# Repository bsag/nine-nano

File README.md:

# Nine keyboard

The Nine is a tiny 18-key split, wireless, ergonomic split keyboard, heavily inspired by Ben Vallack's [Piano 2](https://www.pcbway.com/project/shareproject/The_Piano_by_Ben_Vallack_Ultra_minimal_18_key_keyboard_5b2c99e1.html). I tried out his design and loved it, but wanted to [tweak the physical layout](https://www.rousette.org.uk/archives/introducing-the-nine-keyboard/) a bit to fit my hands and my use case better. It uses Nice!Nano V2 BLE-equipped controllers, and (optionally) Nice!View displays to show information like the connected BLE profile, battery level and layer name. You can read more about this keyboard and the design decisions I made here: [Introducing the Nine keyboard](https://www.rousette.org.uk/archives/introducing-the-nine-keyboard/) and [Nine keyboard Part 2 - the case](https://www.rousette.org.uk/archives/nine-keyboard-part-2-the-case/).

The PCB was generously sponsored by [PCBWay](https://www.pcbway.com/), who paid for the boards. I also got the case printed at PCBWay but paid for that myself. They did a fantastic, high quality job with both and I can highly recommend them. I would like to thank them for their sponsorship and support.

Note that while I provide the `.stl` files for a case which fits the PCB here and works well, I will probably tweak the case (and possibly the PCB design) a bit in future to provide better protection for the displays and controllers, and also possibly provide more options for case designs. If/when I do that, I will add a 'v2' of the case and PCB if necessary here. I may also create a version using the Seeed XIAO BLE controller, which is smaller physically and also slightly cheaper to buy (which is why I have called this repo 'nine-nano'!) In the meantime, I have provided all the necessary source KiCad files and the [Shapr3D](https://www.shapr3d.com/) source files if you want to adapt either design.

## PCB

All the PCB files are [here](pcb/). If you want to fabricate and build the keyboard, the easiest route is to upload the [zip file containing the Gerbers](pcb/nine-nano-gerbers.zip) to a PCB fabrication house like [PCBWay](https://www.pcbway.com/). I have written a [build guide](docs/build_guide.md) which should help you when soldering and assembling the board.

If you need information about how the board is wired up, PDFs of the [schematic](docs/nine_nano_schematic.pdf) and [PCB](docs/nine_nano_pcb.pdf) are provided, or you can open the [project](pcb/nine-nano.kicad_pro) in KiCad to alter the design yourself.

## Case

The `.stl` files needed to build the case, as well as the [Shapr3D source file](case/nine%20case.shapr) are in the [case](case/) directory. You will also find a file there with a basic 3D model of the PCB plus the main board components if you need a reference to build your own case. It's pretty bad though, as I couldn't figure out how to export the model with the surface-mounted components included. If you know how to improve this, please let me know --- it would have made designing the case much easier!

The [build guide](docs/build_guide.md) includes a section on getting the case printed and assembled too. Note that I have only got the case printed in resin, so I cannot guarantee that the tolerances etc. would be correct for printing in PLA or other materials. 

## Firmware

The [ZMK firmware](https://github.com/bsag/zmk-config-nine/) for this keyboard is in a separate repository, which you can fork if you would like to alter the keymapping. Instructions for downloading the firmware are in the [build guide](docs/build_guide.md). 

## Build guide

The build guide for the PCB and case can be found [here](docs/build_guide.md).

## Credits

As previously mentioned, this design is heavily inspired by Ben Vallack's [Piano 2](https://www.pcbway.com/project/shareproject/The_Piano_by_Ben_Vallack_Ultra_minimal_18_key_keyboard_5b2c99e1.html) and the layout he designed. I also used items from various repositories on Github for symbols and footprints to use in KiCad, such as [perigoso's keyswitch library](https://github.com/perigoso/keyswitch-kicad-library), [footstan's kbd library](https://github.com/foostan/kbd), and [crides kleeb library](https://github.com/crides/kleeb). 

Many thanks to the team at PCBWay for their help and support, particularly Liam.

The case design is my own, but I was hugely inspired by [Geist's TOTEM keyboard and case](https://github.com/GEIGEIGEIST/TOTEM), and his excellent build guide. Until seeing his case, I had no idea that you could print in transparent resin, which influenced a lot of my design decisions. He also has a beautiful build guide, which my poor illustration skills cannot hope to live up to!

Last but not least, I have asked a lot of questions and had invaluable advice from many people on the ZMK and Nice Keyboards Discords, including @petejohanson and @TweetyDaBird among others --- thanks for all who gave their time to help me, or who have open sourced their PCB designs, as this was really useful to check my work as I progressed with the designs ♥️. 

## Licence

This work is licenced with an [MIT license](LICENSE).

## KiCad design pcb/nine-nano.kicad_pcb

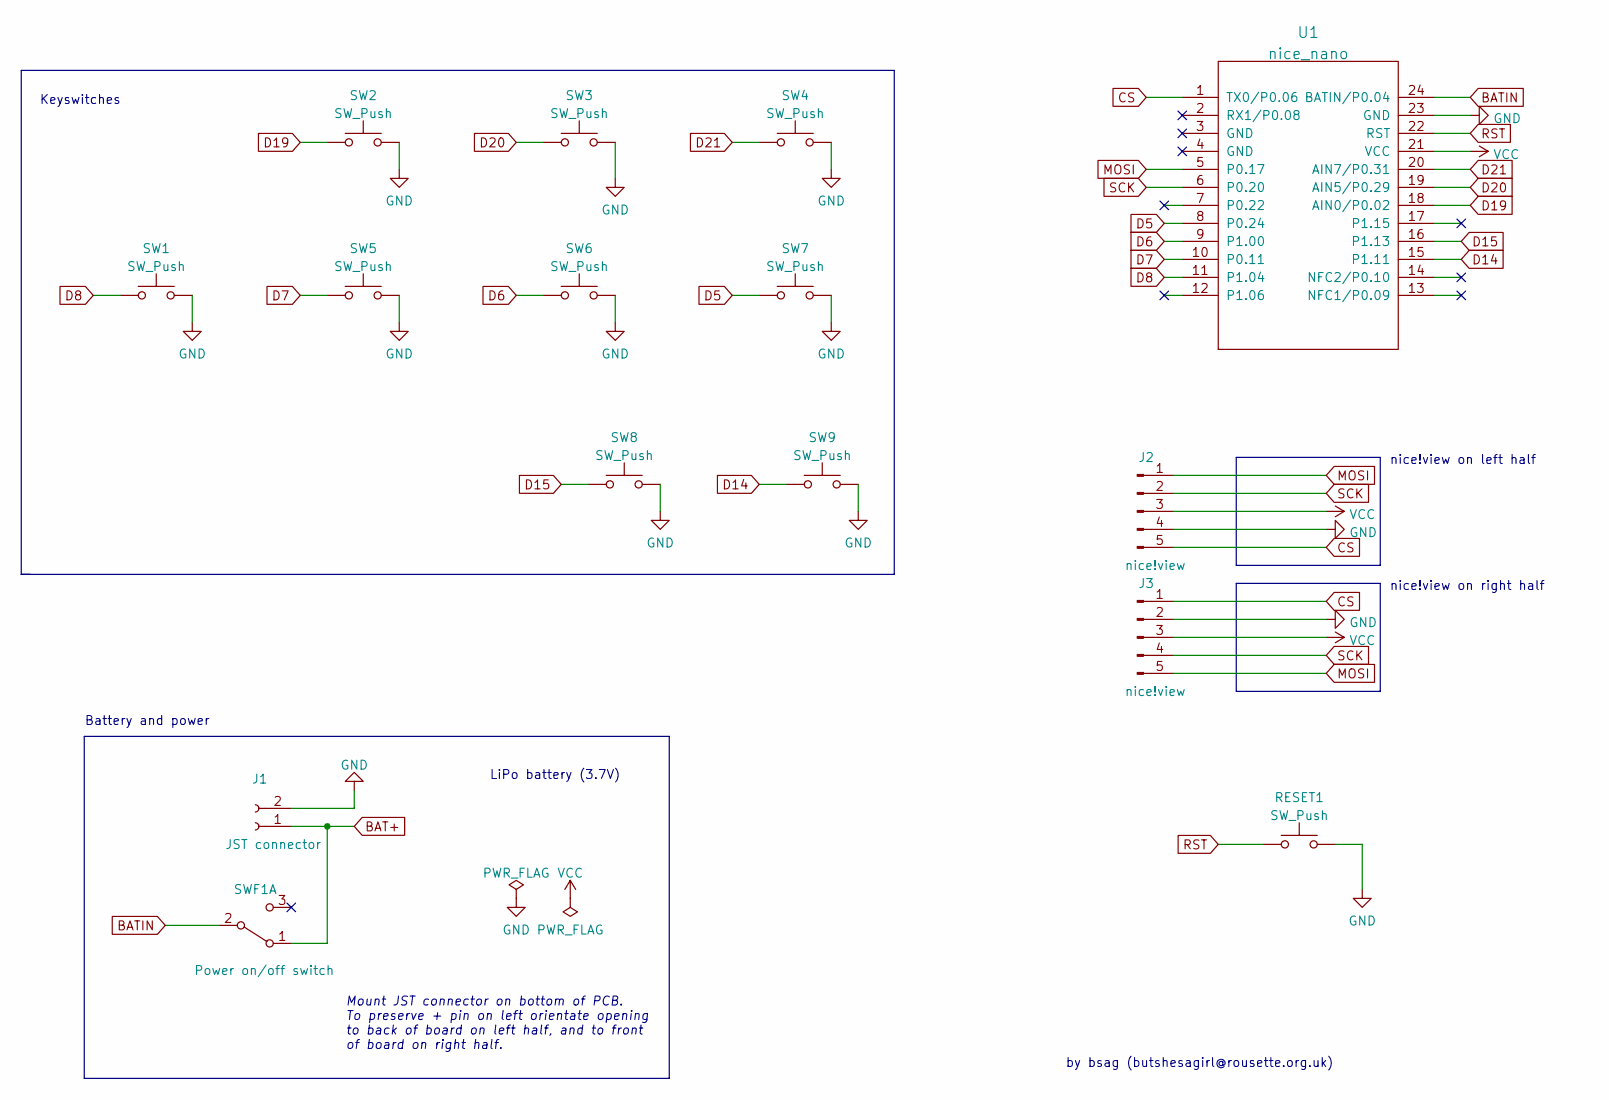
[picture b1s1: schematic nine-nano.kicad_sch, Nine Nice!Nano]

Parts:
J1: JST connector; JST-ZH-2p-1.5
J2, J3: nice!view; OLED_5Pin
RESET1: SW_Push; b3u1000p
SW1, SW8, SW9: SW_Push; pg1350-rev-hs-1.25U
SW2, SW3, SW4, SW5, SW6, SW7: SW_Push; pg1350-rev-hs-1U
SWF1: Power on/off switch; pwr-sw-smd-pcm12
U1: nice_nano; nice-nano-no-rev

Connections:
BAT+: J1.1, SWF1.1 (A)
BATIN: SWF1.2 (B), U1.24 (BATIN/P0.04)
CS: J2.5, J3.1, U1.1 (TX0/P0.06)
D5: SW7.1, U1.8 (P0.24)
D6: SW6.1, U1.9 (P1.00)
D7: SW5.1, U1.10 (P0.11)
D8: SW1.1, U1.11 (P1.04)
D14: SW9.1, U1.15 (P1.11)
D15: SW8.1, U1.16 (P1.13)
D19: SW2.1, U1.18 (AIN0/P0.02)
D20: SW3.1, U1.19 (AIN5/P0.29)
D21: SW4.1, U1.20 (AIN7/P0.31)
GND: J1.2, J2.4, J3.2, RESET1.2, SW1.2, SW2.2, SW3.2, SW4.2, SW5.2, SW6.2, SW7.2, SW8.2, SW9.2, U1.23 (GND)
MOSI: J2.1, J3.5, U1.5 (P0.17)
RST: RESET1.1, U1.22 (RST)
SCK: J2.2, J3.4, U1.6 (P0.20)
VCC: J2.3, J3.3, U1.21 (VCC)

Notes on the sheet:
by bsag (butshesagirl@rousette.org.uk)
LiPo battery (3.7V)
Mount JST connector on bottom of PCB. To preserve + pin on left orientate opening to back of board on left half, and to front of board on right half.
nice!view on right half
Keyswitches
nice!view on left half
Battery and power

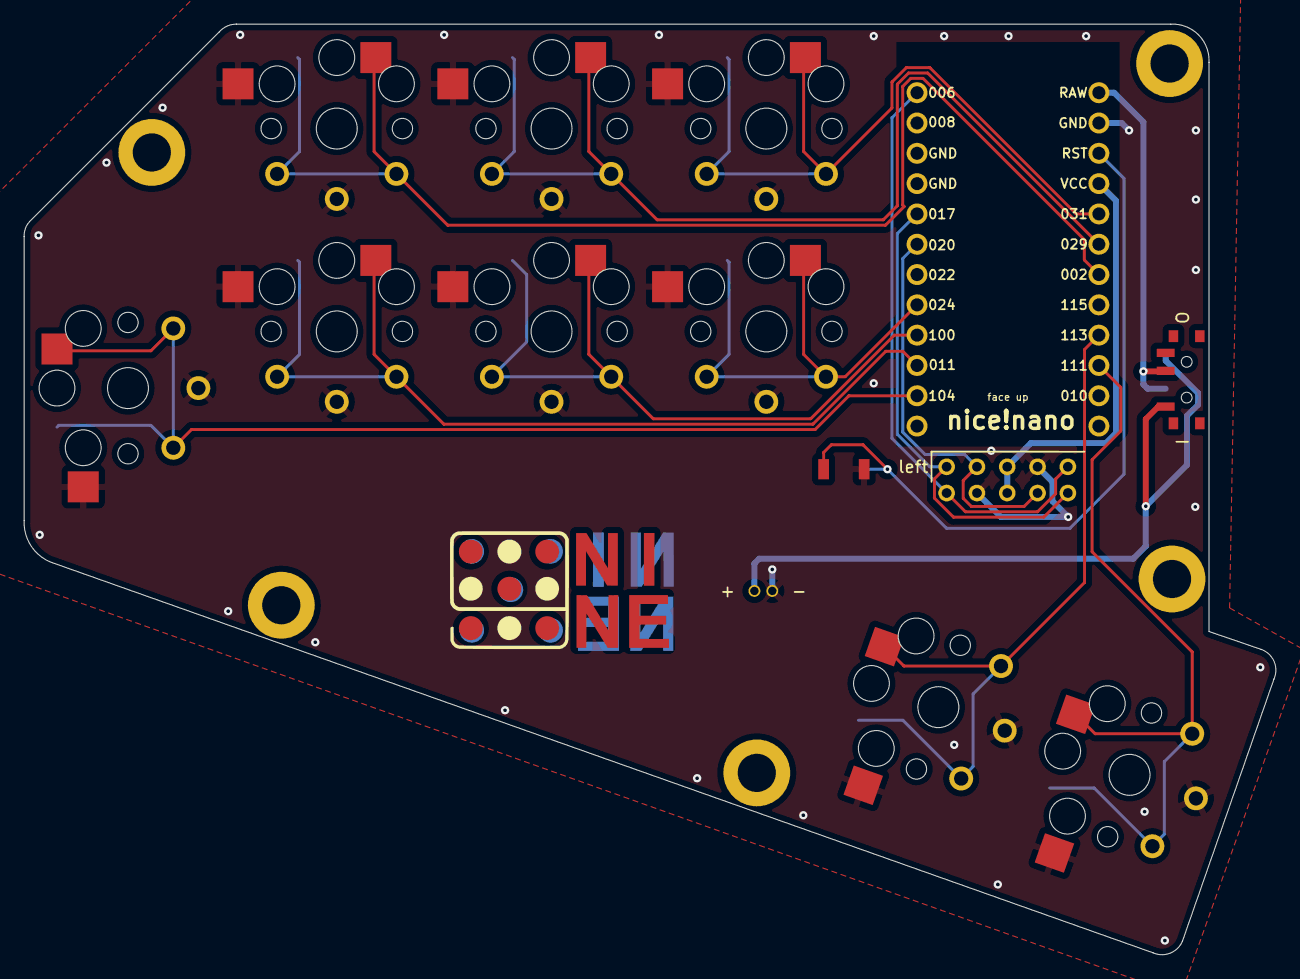
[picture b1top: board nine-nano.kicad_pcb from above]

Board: 2 copper layers, 104.9 x 78.0 mm, 15 parts (0 on the bottom side), 17 nets.

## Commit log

2023-01-01 Create LICENSE
2023-01-04 Added links to blog posts and sponsorship info
2023-01-04 Fixed typo
